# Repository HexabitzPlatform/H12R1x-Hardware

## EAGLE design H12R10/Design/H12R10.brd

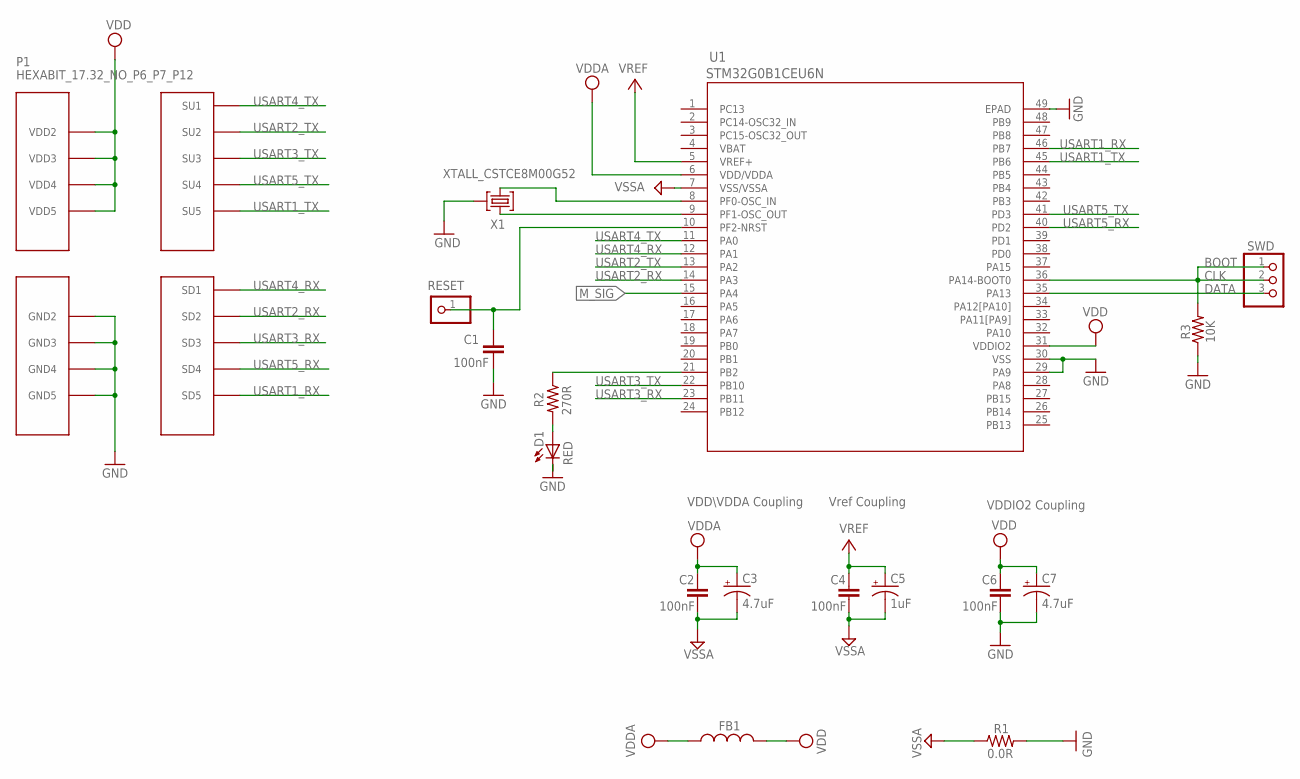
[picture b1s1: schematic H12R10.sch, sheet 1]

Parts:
C1, C2, C4, C6: 100nF; C-0603
C3, C7: 4.7uF; C-0805-POL
C5: 1uF; C-0805-POL
D1: RED; VLMS1300-GS08; MPN VLMS1300-GS08
FB1: FB-0603
P1: HEXABIT_17.32_NO_P6_P7_P12
R1: 0.0R; R-0603
R2: 270R; R-0603
R3: 10K; R-0603
RESET: R; 1X01
SWD: PINHD-1X3SWD; SWD
U1: STM32G0B1CEU6N; HEXABITZ_ICS_QFN_B1CEU6_STM-L
X1: XTALL_CSTCE8M00G52

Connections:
CLK: R3.2, SWD.1, SWD.2, U1.36 (PA14-BOOT0)
DATA: SWD.3, U1.35 (PA13)
GND: C1.2, C6.2, C7.2 (-), D1.C, P1.PAD_PD8 (GND2), P1.PAD_PD9 (GND3), P1.PAD_PD10 (GND4), P1.PAD_PD11 (GND5), R1.2, R3.1, U1.29 (PA9), U1.30 (VSS), U1.49 (EPAD), X1.P$2 (2)
M_SIG: U1.15 (PA4); also elsewhere on the board
unnamed: D1.A, R2.2
unnamed: R2.1, U1.21 (PB2)
unnamed: U1.9 (PF1-OSC_OUT), X1.P$1 (1)
unnamed: U1.8 (PF0-OSC_IN), X1.P$3 (3)
unnamed: C1.1, RESET.1, U1.10 (PF2-NRST)
USART1_RX: P1.PAD_PD5 (SD5), U1.46 (PB7)
USART1_TX: P1.PAD_PU5 (SU5), U1.45 (PB6)
USART2_RX: P1.PAD_PD2 (SD2), U1.14 (PA3)
USART2_TX: P1.PAD_PU2 (SU2), U1.13 (PA2)
USART3_RX: P1.PAD_PD3 (SD3), U1.23 (PB11)
USART3_TX: P1.PAD_PU3 (SU3), U1.22 (PB10)
USART4_RX: P1.PAD_PD1 (SD1), U1.12 (PA1)
USART4_TX: P1.PAD_PU1 (SU1), U1.11 (PA0)
USART5_RX: P1.PAD_PD4 (SD4), U1.40 (PD2)
USART5_TX: P1.PAD_PU4 (SU4), U1.41 (PD3)
VBAT: U1.4 (VBAT)
VDD: C6.1, C7.1 (+), FB1.2, P1.PAD_PU8 (VDD2), P1.PAD_PU9 (VDD3), P1.PAD_PU10 (VDD4), P1.PAD_PU11 (VDD5), U1.31 (VDDIO2)
VDDA: C2.1, C3.1 (+), FB1.1, U1.6 (VDD/VDDA); also elsewhere on the board
VREF: C4.1, C5.1 (+), U1.5 (VREF+); also elsewhere on the board
VSSA: C2.2, C3.2 (-), C4.2, C5.2 (-), R1.1, U1.7 (VSS/VSSA); also elsewhere on the board

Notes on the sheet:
Vref Coupling
VDDIO2 Coupling
VDD\VDDA Coupling
BOOT

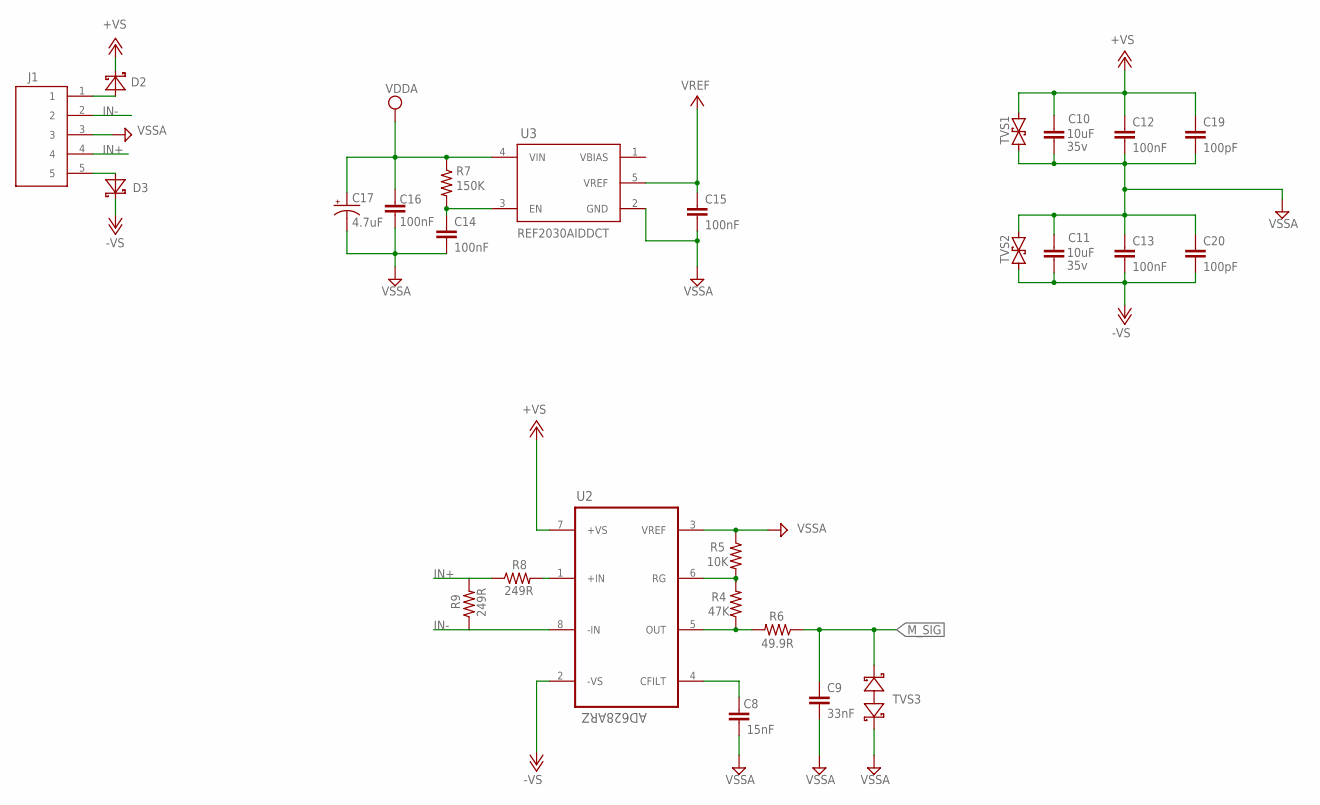
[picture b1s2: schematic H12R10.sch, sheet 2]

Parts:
C8: 15nF; C-0603
C9: 33nF; C-0603
C10, C11: C-0805; VOLTAGE_RATING 35v; MPN GRM21BR6YA106ME43K
C12, C13: 100nF; C-0603; MPN C1608X7R1H104K080AA
C14, C15, C16: 100nF; C-0603
C17: 4.7uF; C-0805-POL
C19, C20: 100pF; C-0603; MPN C1608X7R1H104K080AA
D2, D3: DIOD-SOD-123; SOD123
J1: 1984646
R4: 47K; R-0603
R5: 10K; R-0603
R6: 49.9R; R-0603
R7: 150K; R-0603
R8, R9: 249R; R-0603
TVS1, TVS2: SMBJ30CA; DO214AA
TVS3: BOURNS_CDSOD323-T03SCBOURNS_CDSOD323-T03SC_0_0; BOURNS_CDSOD323-T03SC_0
U2: AD628ARZ; SOIC127P600X175-8N
U3: TEXAS_INSTRUMENTS_REF2033AIDDCRTEXAS_INSTRUMENTS_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; TEXAS_INSTRUMENTS_REF2033AIDDCR_2; MPN REF2030AIDDCT

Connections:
+VS: C10.1, C12.1, C19.1, D2.2 (C), TVS1.C (2), U2.7 (+VS)
-VS: C11.2, C13.2, C20.2, D3.2 (C), TVS2.A (1), U2.2 (-VS)
CFILT: C8.1, U2.4 (CFILT)
IN+: J1.4, R8.1, R9.2
IN-: J1.2, R9.1, U2.8 (-IN)
M_SIG: C9.1, R6.1, TVS3.2 (C); also elsewhere on the board
unnamed: D3.1 (A), J1.5
unnamed: D2.1 (A), J1.1
unnamed: C14.1, R7.2, U3.3 (EN)
unnamed: R8.2, U2.1 (+IN)
OUT: R4.1, R6.2, U2.5 (OUT)
RG: R4.2, R5.2, U2.6 (RG)
VBIAS: U3.1 (VBIAS)
VDDA: C16.1, C17.1 (+), R7.1, U3.4 (VIN); also elsewhere on the board
VREF: C15.1, U3.5 (VREF); also elsewhere on the board
VSSA: C8.2, C9.2, C10.2, C11.1, C12.2, C13.1, C14.2, C15.2, C16.2, C17.2 (-), C19.2, C20.1, J1.3, R5.1, TVS1.A (1), TVS2.C (2), TVS3.1 (A), U2.3 (VREF), U3.2 (GND); also elsewhere on the board

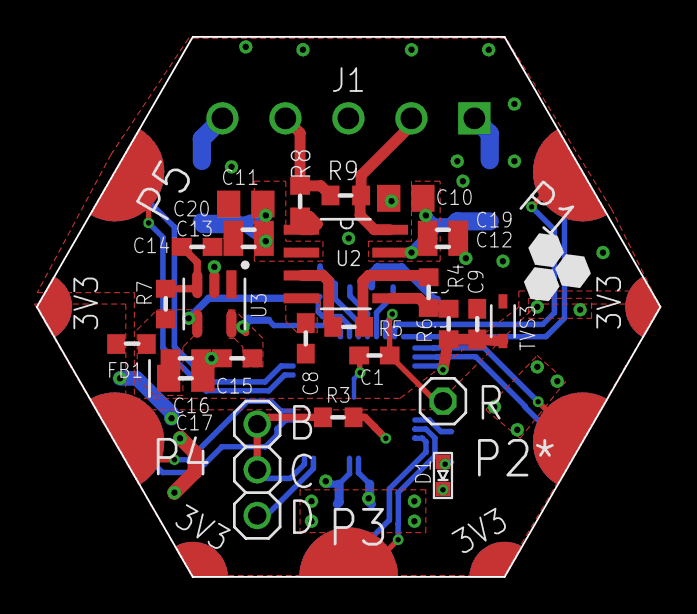
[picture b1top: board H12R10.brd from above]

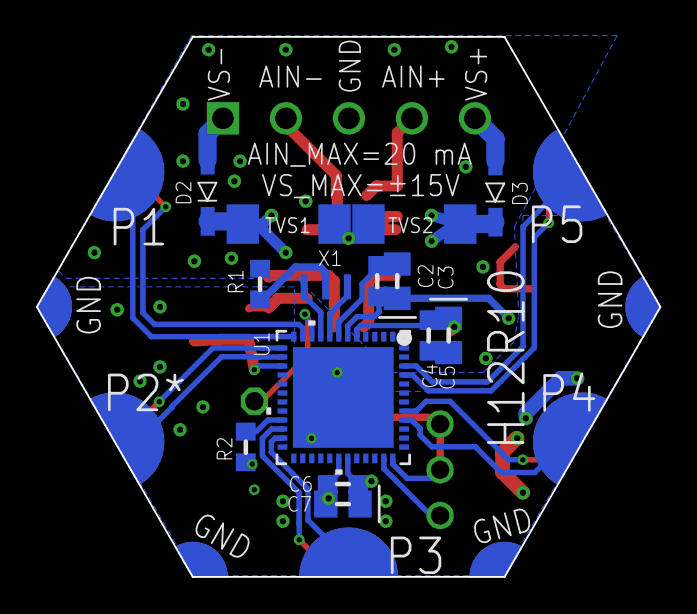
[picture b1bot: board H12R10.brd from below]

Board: 2 copper layers, 34.6 x 30.0 mm, 43 parts (14 on the bottom side), 34 nets.

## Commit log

2023-11-05 -The complete design
2023-11-05 -Fix BOM

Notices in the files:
parts and their libraries:
HEXABITZ_ICs: COPYRIGHT: Copyright (C) 2022 Ultra Librarian. All rights reserved.
